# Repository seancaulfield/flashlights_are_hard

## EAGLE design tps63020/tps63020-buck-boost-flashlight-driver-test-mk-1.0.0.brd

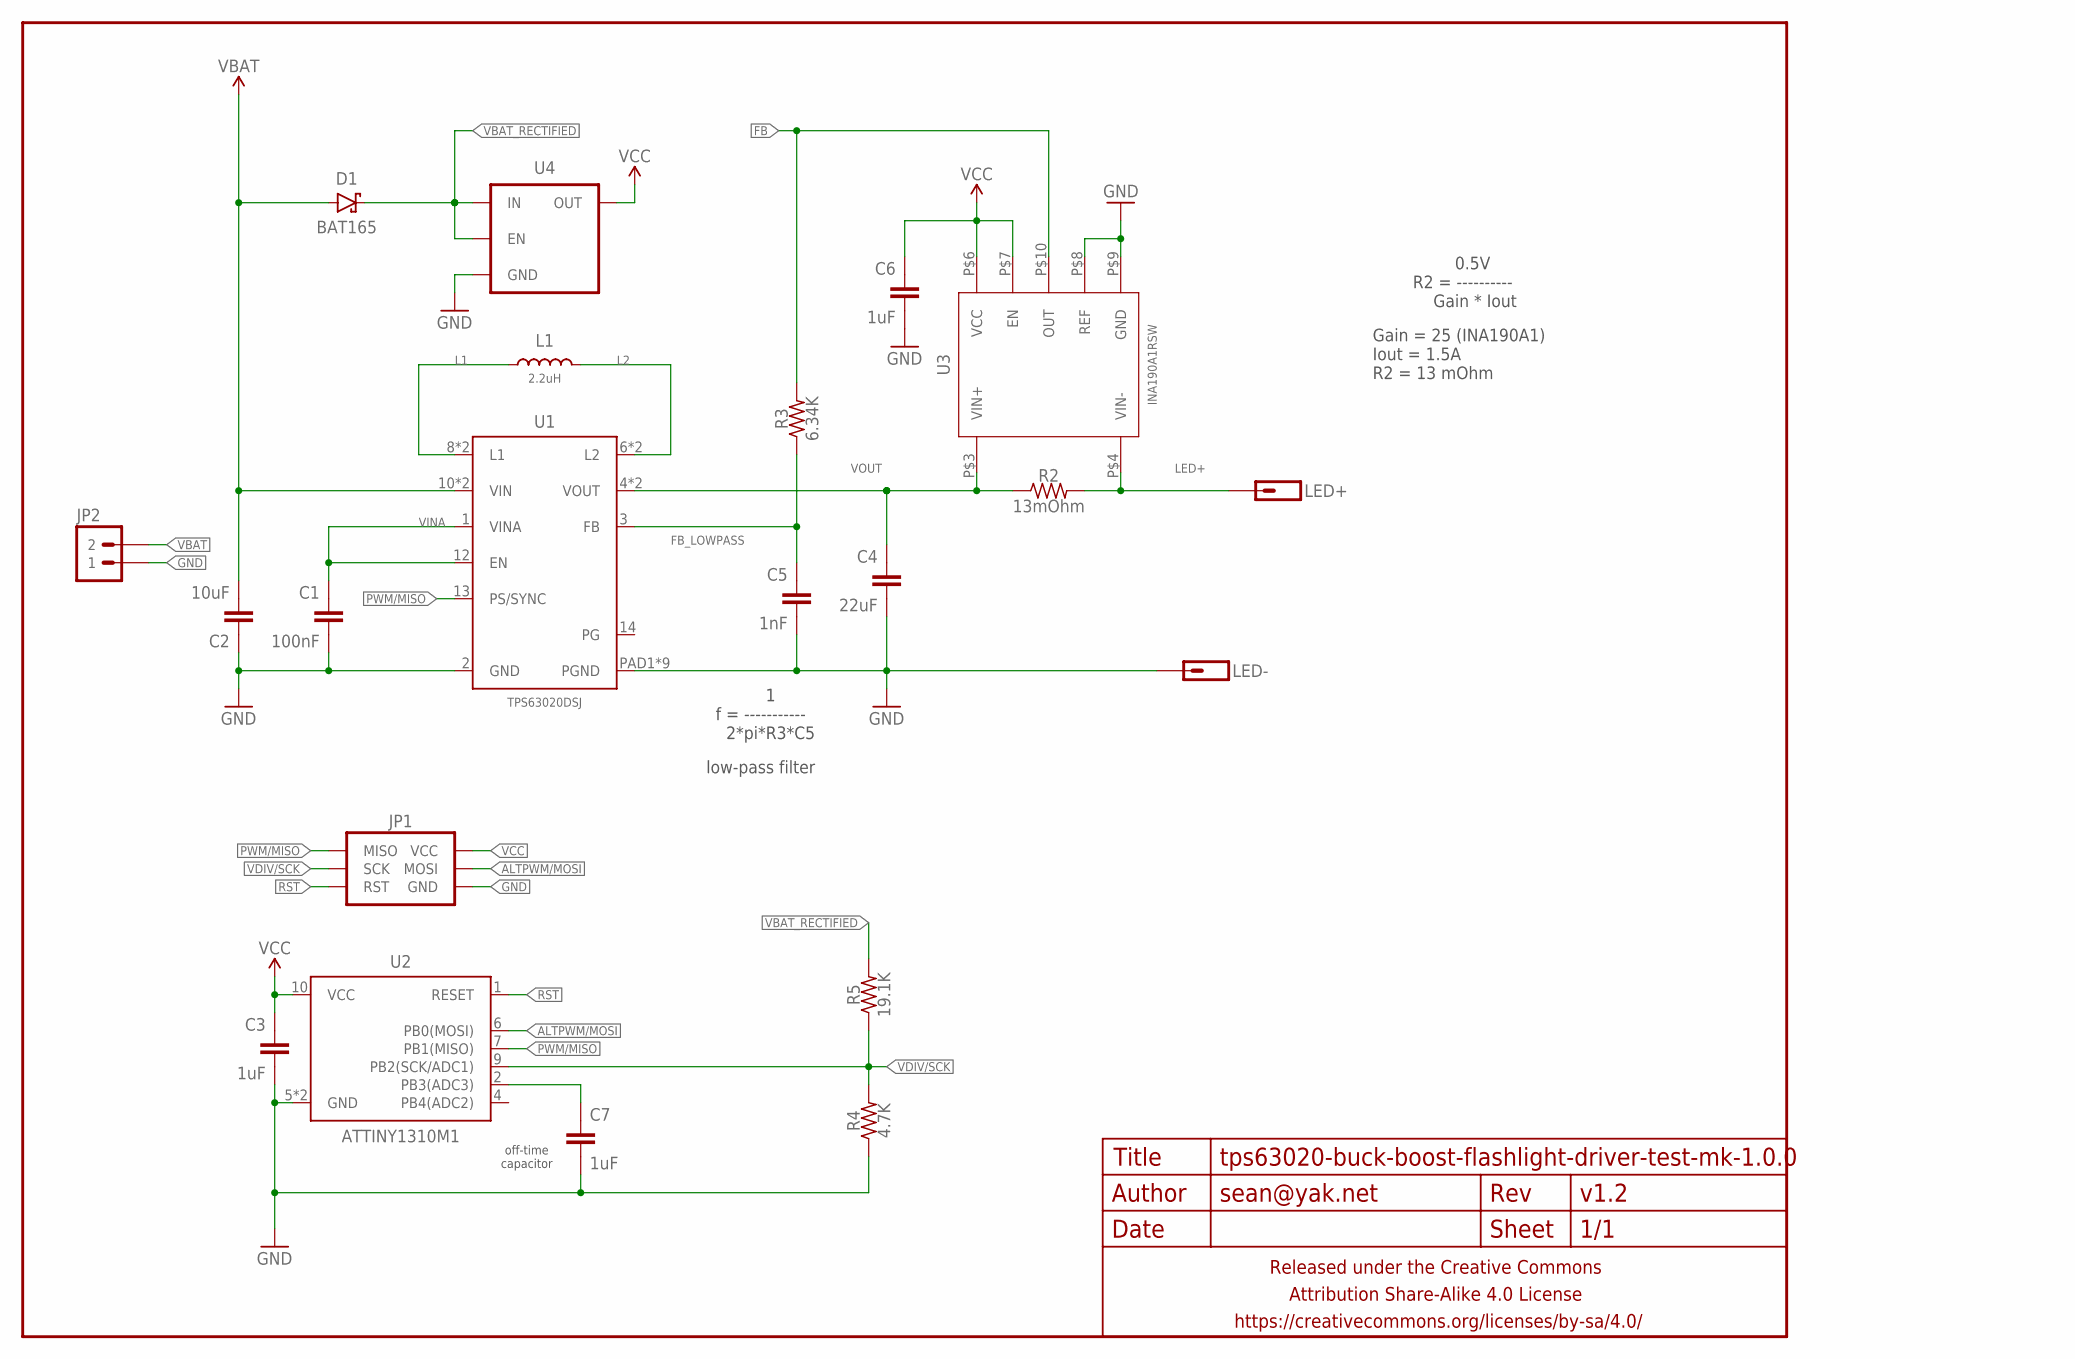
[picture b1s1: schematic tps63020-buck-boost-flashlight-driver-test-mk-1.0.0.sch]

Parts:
C1: 100nF; C0402
C2: 10uF; C0805-TIGHTER
C3, C6, C7: 1uF; C0402
C4: 22uF; C0805-TIGHTER
C5: 1nF; C0402
D1: BAT165; SOD323-SCHOTTKY
FRAME1: FRAME-LETTERNO_PACKAGE; DUMMY
JP1: AVR_SPI_PRG_6PTH-1.27MM; 2X3-1.27MM-PTH
JP2: M02PTH-2MM; 1X02-2MM-PTH
L1: 2.2uH; XAL50X0
LED+: M01PTH-1MM-CIR-NS; 1X01-1MM-CIR-NS
LED-: M01PTH-1MM-CIR-NS; 1X01-1MM-CIR-NS
R2: 13mOhm; R0805-TIGHTER
R3: 6.34K; R0402
R4: 4.7K; R0402
R5: 19.1K; R0402
U1: TPS63020DSJ; VSON-14-4MMX3MM
U2: ATTINY1310M1; QFN10(2X5)
U3: INA190A1RSW; UQFN-10
U4: V_REG_ENTLV700; SC70

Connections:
ALTPWM/MOSI: JP1.4 (MOSI), U2.6 (PB0(MOSI))
FB: R3.2, U3.P$10 (OUT)
FB_LOWPASS: C5.1, R3.1, U1.3 (FB)
GND: C1.2, C2.1, C3.2, C4.2, C5.2, C6.2, C7.2, JP1.6 (GND), JP2.P$1 (1), LED-.1, R4.1, U1.2 (GND), U1.PAD1 (PGND), U1.PAD2 (PGND), U1.PAD3 (PGND), U1.PAD4 (PGND), U1.PAD5 (PGND), U1.PAD6 (PGND), U1.PAD7 (PGND), U1.PAD8 (PGND), U1.PADCENTER (PGND), U2.5 (GND), U2.PAD (GND), U3.P$8 (REF), U3.P$9 (GND), U4.2 (GND)
L1: L1.P$1 (1), U1.8 (L1), U1.9 (L1)
L2: L1.P$2 (2), U1.6 (L2), U1.7 (L2)
LED+: LED+.1, R2.2, U3.P$4 (VIN-)
unnamed: C7.1, U2.2 (PB3(ADC3))
PWM/MISO: JP1.1 (MISO), U1.13 (PS/SYNC), U2.7 (PB1(MISO))
RST: JP1.5 (RST), U2.1 (RESET)
VBAT: C2.2, D1.A, JP2.P$2 (2), U1.10 (VIN), U1.11 (VIN)
VBAT_RECTIFIED: D1.C, R5.2, U4.1 (IN), U4.3 (EN)
VCC: C3.1, C6.1, JP1.2 (VCC), U2.10 (VCC), U3.P$6 (VCC), U3.P$7 (EN), U4.5 (OUT)
VDIV/SCK: JP1.3 (SCK), R4.2, R5.1, U2.9 (PB2(SCK/ADC1))
VINA: C1.1, U1.1 (VINA), U1.12 (EN)
VOUT: C4.1, R2.1, U1.4 (VOUT), U1.5 (VOUT), U3.P$3 (VIN+)

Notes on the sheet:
off-time capacitor
1 f = ----------- 2*pi*R3*C5
0.5V R2 = ---------- Gain * Iout
low-pass filter
Gain = 25 (INA190A1) Iout = 1.5A R2 = 13 mOhm

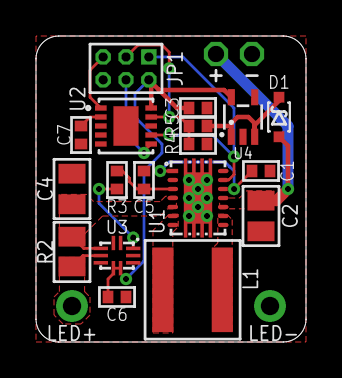
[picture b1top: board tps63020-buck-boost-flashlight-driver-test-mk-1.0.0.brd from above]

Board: 2 copper layers, 15.0 x 17.0 mm, 22 parts (0 on the bottom side), 16 nets.

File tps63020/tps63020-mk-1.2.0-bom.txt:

TPS63020 Buck-Boost Flashlight Driver 17mm Mk 1.2
TPS63020 based buck-boost LED driver in 17mm / 4 layers, with 1.27mm ISP pogo header on bottom side for in-flashlight programming.

#### Bill of Materials (BOM)
U1	TPS63020DSJR  
U2	ATTINY13A-MMU  
U3	INA190A1IRSWR [1]  
U4	TLV70025DCKR [2]  
C1	100nF 0402  
C2	22uF 16V 0805  
C3	1uF 0402  
C4	47uF 25V 1206  
C5	1nF 0402  
C6	1uF 0402  
C7	1uF 0402  
R2	13mOhm 1206 [3]  
R3	6.8K 0402  
R4	4.7K 0402  
R5	19.1K 0402  

1) Make sure to get the A1 version, as others have different gain which changes the power output.  
2) Any 2-3V LDO should do.  
3) Current sense resistor, 13mOhm is for about 1.5A out.  

Rsense = 0.5V / (Iout \* gain) = 0.5V / (Iout \* 25)

| Iout (mA) | Rsense (mOhm) |
|-----------|---------------|
|      1000 |            20 |
|      1500 |            13 |
|      2000 |            10 |

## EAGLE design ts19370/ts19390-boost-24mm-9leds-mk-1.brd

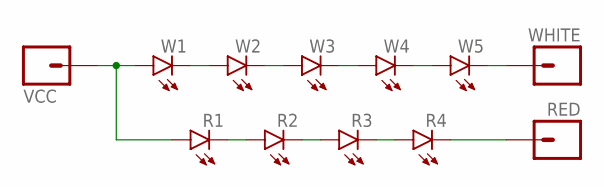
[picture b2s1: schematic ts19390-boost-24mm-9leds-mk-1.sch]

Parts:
R1, R2, R3, R4: LED5MM_SHORTPADS
RED: M01PTH-NS-NOTSUCK; 1X01NSATALL
VCC: M01PTH-NS-NOTSUCK; 1X01NSATALL
W1, W2, W3, W4, W5: LED5MM_SHORTPADS
WHITE: M01PTH-NS-NOTSUCK; 1X01NSATALL

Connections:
unnamed: W1.K (C), W2.A
unnamed: W2.K (C), W3.A
unnamed: W3.K (C), W4.A
unnamed: W4.K (C), W5.A
unnamed: R1.K (C), R2.A
unnamed: R2.K (C), R3.A
unnamed: W5.K (C), WHITE.1
unnamed: R3.K (C), R4.A
unnamed: R4.K (C), RED.1
unnamed: R1.A, VCC.1, W1.A

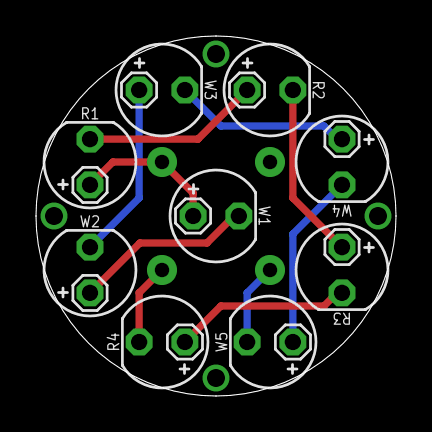
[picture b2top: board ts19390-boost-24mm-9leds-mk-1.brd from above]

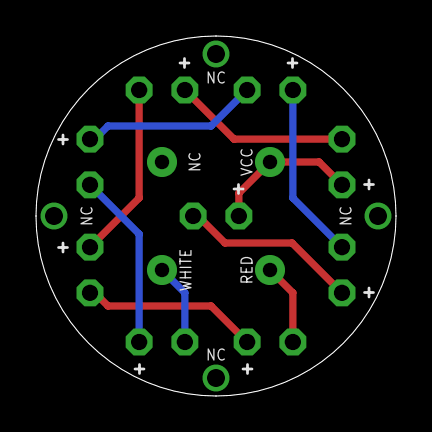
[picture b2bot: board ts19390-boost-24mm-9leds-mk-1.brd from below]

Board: 2 copper layers, 20.0 x 20.0 mm, 12 parts (3 on the bottom side), 10 nets.

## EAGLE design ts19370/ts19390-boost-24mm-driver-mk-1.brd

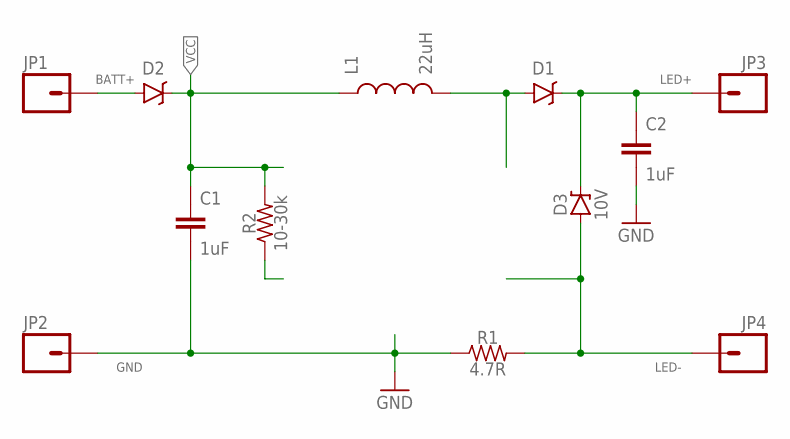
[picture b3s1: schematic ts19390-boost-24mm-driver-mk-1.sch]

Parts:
C1, C2: 1uF; C0805
D1, D2: B340A; SOD123-SCHOTTKY
D3: 10V; SOD123-ZENER
JP1, JP2, JP3, JP4: M01PTH; 1X01
L1: 22uH; TAIYO-YUDEN-30XX
R1: 4.7R; R0805
R2: 10-30k; R0603

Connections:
BATT+: D2.A, JP1.1
GND: C1.2, C2.2, JP2.1, R1.1
LED+: C2.1, D1.C, D3.C, JP3.1
LED-: D3.A, JP4.1, R1.2
unnamed: D1.A, L1.2
VCC: C1.1, D2.C, L1.1, R2.2

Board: 2 copper layers, 12 parts (0 on the bottom side), 6 nets, no tracks yet.

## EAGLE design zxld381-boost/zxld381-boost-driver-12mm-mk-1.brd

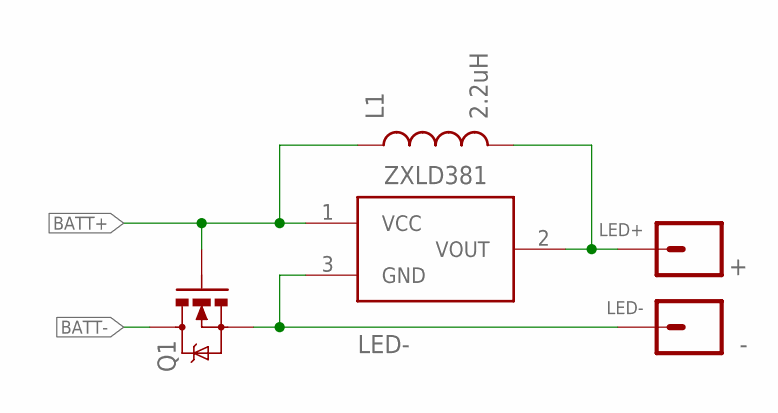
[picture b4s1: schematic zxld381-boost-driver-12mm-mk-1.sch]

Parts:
+: M01PTH-NS-NOTSUCK; 1X01NSATALL
-: M01PTH-NS-NOTSUCK; 1X01NSATALL
L1: 2.2uH; 0805
Q1: MOSFET-NCHANNELIRLML2502; SOT23
ZXLD381: ZXLD381; SOT23-3

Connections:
BATT+: L1.1, Q1.1 (G), ZXLD381.1 (VCC)
BATT-: Q1.3 (D)
LED+: +.1, L1.2, ZXLD381.2 (VOUT)
LED-: -.1, Q1.2 (S), ZXLD381.3 (GND)

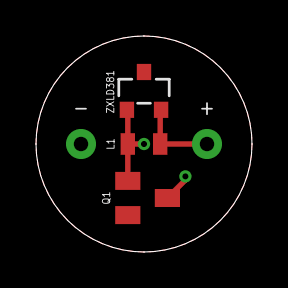
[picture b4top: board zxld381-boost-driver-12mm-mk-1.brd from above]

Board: 2 copper layers, 12.0 x 12.0 mm, 5 parts (0 on the bottom side), 3 nets.

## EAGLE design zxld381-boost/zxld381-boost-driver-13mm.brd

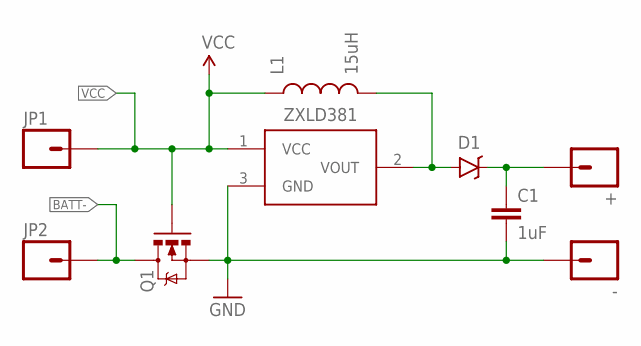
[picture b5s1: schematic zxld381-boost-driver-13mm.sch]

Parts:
+: M01PTH-KIT; 1X01-KIT
-: M01NOSILK-KIT; 1X01NS-KIT
C1: 1uF; C0805
D1: PMEG4005EJ; SOD-323
JP1, JP2: M01NOT-A-VIA-NOPE; 1X01_NOSILK_NOSTOP
L1: 15uH; 0805
Q1: MOSFET-NCHANNELRYM002N05; VMT3
ZXLD381: ZXLD381; SOT23-3

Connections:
BATT-: JP2.P$1, Q1.3 (D)
GND: -.1, C1.2, Q1.2 (S), ZXLD381.3 (GND)
unnamed: D1.A, L1.2, ZXLD381.2 (VOUT)
unnamed: +.1, C1.1, D1.C
VCC: JP1.P$1, L1.1, Q1.1 (G), ZXLD381.1 (VCC)

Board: 2 copper layers, 9 parts (0 on the bottom side), 5 nets, no tracks yet.

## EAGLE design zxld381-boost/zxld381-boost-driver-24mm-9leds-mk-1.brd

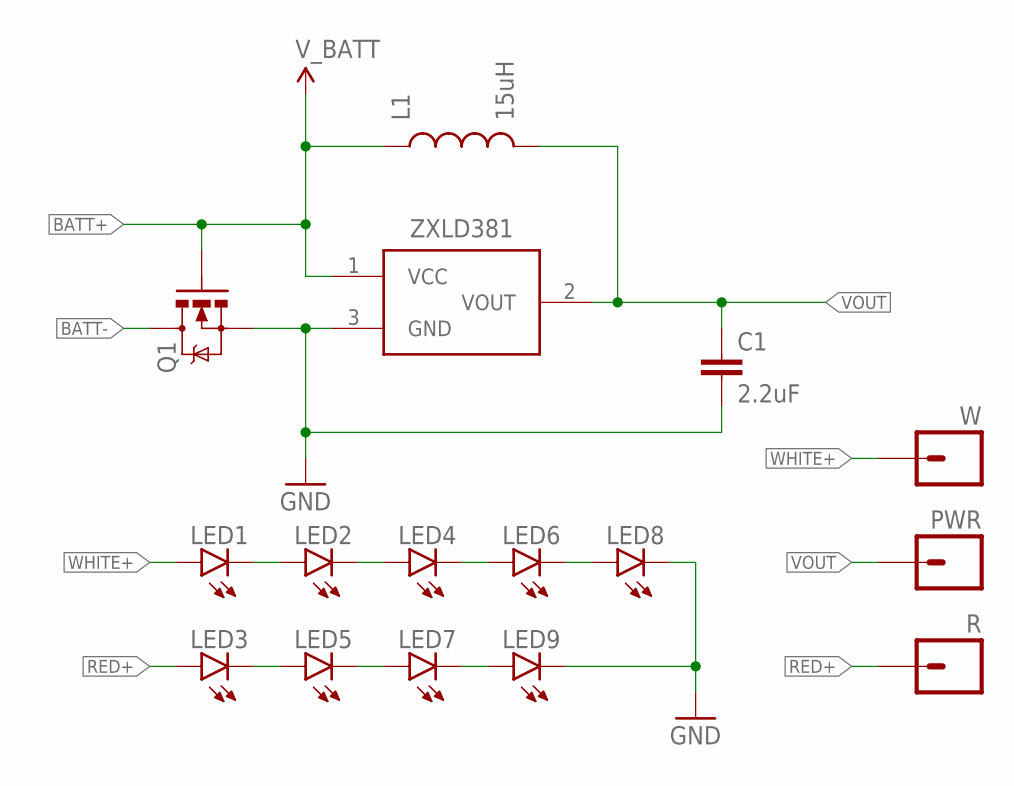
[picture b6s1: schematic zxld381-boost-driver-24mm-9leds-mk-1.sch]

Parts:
C1: 2.2uF; C0805
L1: 15uH; L0805
LED1, LED2, LED3, LED4, LED5, LED6, LED7, LED8, LED9: LED5MM_SHORTPADS
PWR: M01PTH-TINY; 1X01_635UM
Q1: MOSFET-NCHANNELIRLML2502; SOT23
R: M01PTH-TINY; 1X01_635UM
W: M01PTH-TINY; 1X01_635UM
ZXLD381: ZXLD381; SOT23-3

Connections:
BATT+: L1.1, Q1.1 (G), ZXLD381.1 (VCC)
BATT-: Q1.3 (D)
GND: C1.2, LED8.K (C), LED9.K (C), Q1.2 (S), ZXLD381.3 (GND)
unnamed: LED1.K (C), LED2.A
unnamed: LED2.K (C), LED4.A
unnamed: LED4.K (C), LED6.A
unnamed: LED6.K (C), LED8.A
unnamed: LED3.K (C), LED5.A
unnamed: LED5.K (C), LED7.A
unnamed: LED7.K (C), LED9.A
RED+: LED3.A, R.P$1
VOUT: C1.1, L1.2, PWR.P$1, ZXLD381.2 (VOUT)
WHITE+: LED1.A, W.P$1

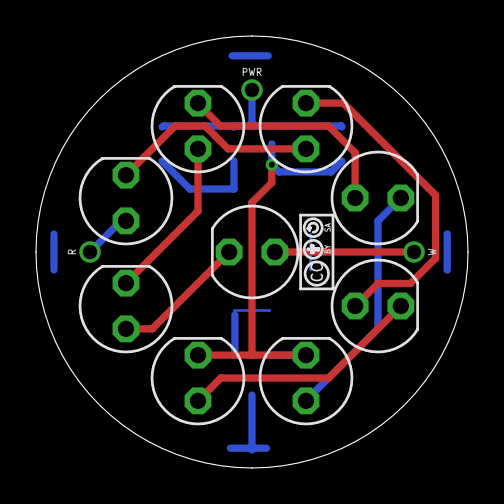
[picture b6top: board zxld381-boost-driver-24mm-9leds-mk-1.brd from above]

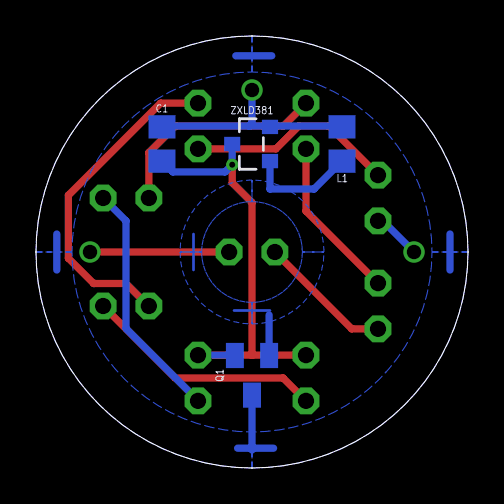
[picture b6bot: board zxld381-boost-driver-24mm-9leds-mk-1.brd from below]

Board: 2 copper layers, 24.0 x 24.0 mm, 17 parts (4 on the bottom side), 12 nets.

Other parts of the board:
U$1: CC-BY-SA-4.0-SMALL

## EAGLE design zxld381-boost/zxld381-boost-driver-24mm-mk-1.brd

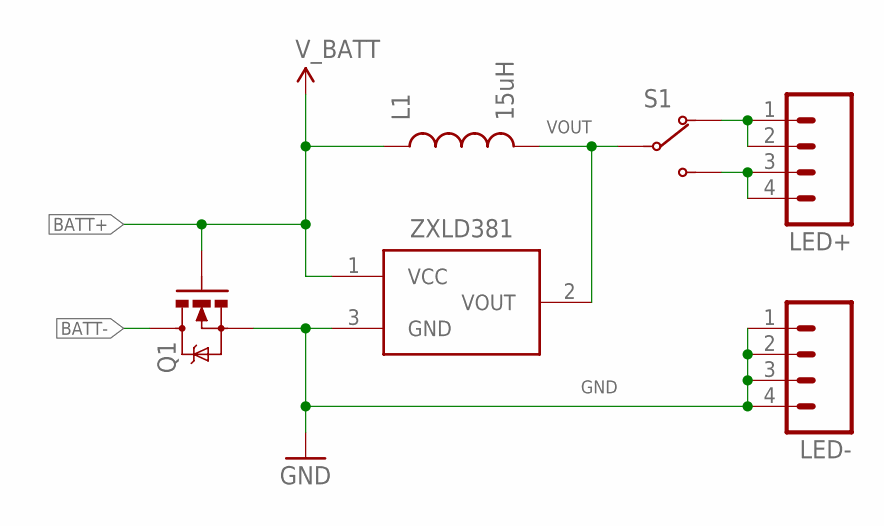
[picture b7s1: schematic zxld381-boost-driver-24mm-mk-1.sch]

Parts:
L1: 15uH; 0805
LED+: M04PTH; 1X04-PTH-VERT
LED-: M04PTH; 1X04-PTH-VERT
Q1: MOSFET-NCHANNELIRLML2502; SOT23
S1: SWITCH-SPDTPTH-RA-2MM; SPDT-RA-2MM
ZXLD381: ZXLD381; SOT23-3

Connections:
BATT+: L1.1, Q1.1 (G), ZXLD381.1 (VCC)
BATT-: Q1.3 (D)
GND: LED-.1, LED-.2, LED-.3, LED-.4, Q1.2 (S), ZXLD381.3 (GND)
unnamed: LED+.1, LED+.2, S1.1 (NC)
unnamed: LED+.3, LED+.4, S1.3 (NO)
VOUT: L1.2, S1.2 (COM), ZXLD381.2 (VOUT)

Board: 2 copper layers, 6 parts (0 on the bottom side), 5 nets, no tracks yet.

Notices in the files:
parts and their libraries:
a_parts: Released under the Creative Commons Attribution Share-Alike 4.0 License
a_parts: https://creativecommons.org/licenses/by-sa/4.0
a_parts: Released under the Creative Commons
